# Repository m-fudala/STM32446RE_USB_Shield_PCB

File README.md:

# USB shield for Nucleo STM32F446RE
A simple shield which enables use of USB through type B receptacle. \
Includes also two places for THT resistors if external USB pull-ups are needed.

 \

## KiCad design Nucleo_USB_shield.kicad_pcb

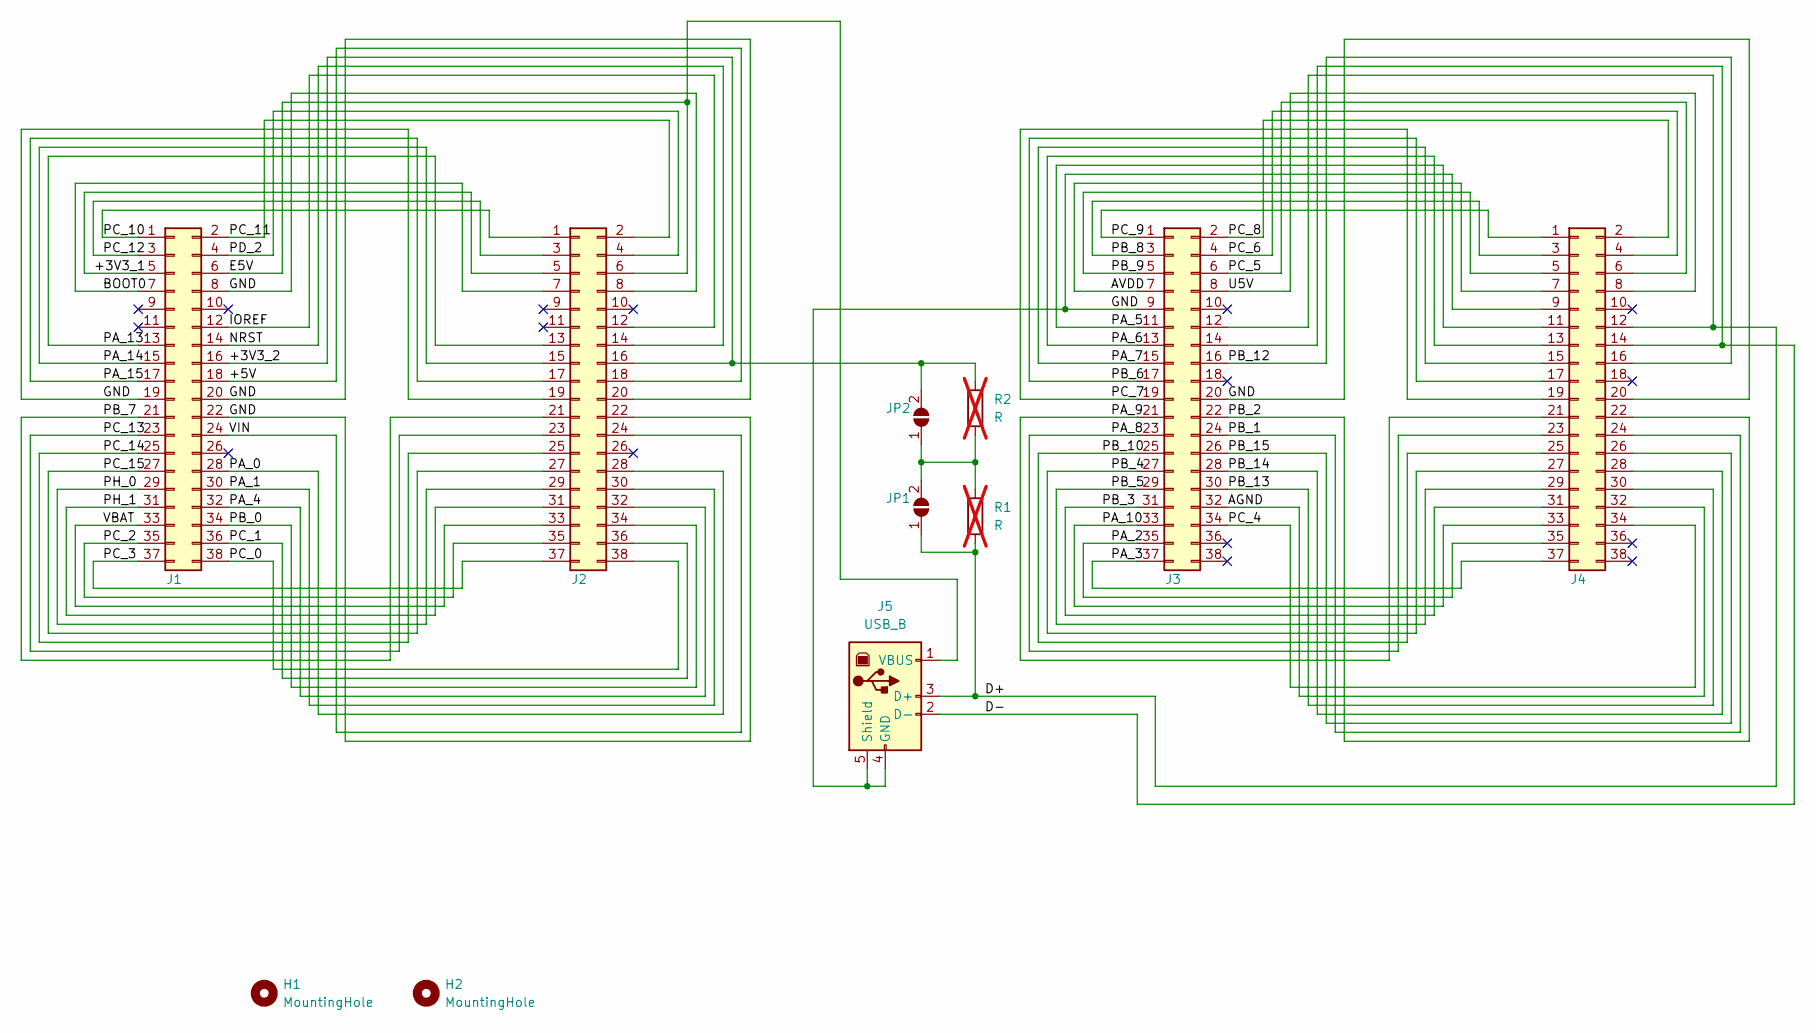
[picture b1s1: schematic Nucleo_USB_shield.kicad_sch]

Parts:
H1, H2: MountingHole; MountingHole_3.2mm_M3
J1, J3: Conn_02x19_Odd_Even; PinSocket_2x19_P2.54mm_Vertical
J2, J4: Conn_02x19_Odd_Even; PinHeader_2x19_P2.54mm_Vertical
J5: USB_B; USB_B_Lumberg_2411_02_Horizontal
JP1, JP2: SolderJumper_2_Open; SolderJumper-2_P1.3mm_Open_RoundedPad1.0x1.5mm
R1, R2: R; R_Axial_DIN0207_L6.3mm_D2.5mm_P7.62mm_Horizontal; not fitted

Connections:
/+3V3_1: J1.5, J2.5
/+3V3_2: J1.16, J2.16, JP2.2 (B), R2.1
/+5V: J1.18, J2.18
/AGND: J3.32, J4.32
/AVDD: J3.7, J4.7
/BOOT0: J1.7, J2.7
/D+: J3.12, J4.12, J5.3 (D+), JP1.1 (A), R1.2
/D-: J3.14, J4.14, J5.2 (D-)
/E5V: J1.6, J2.6, J5.1 (VBUS)
/GND: J1.8, J1.19, J1.20, J1.22, J2.8, J2.19, J2.20, J2.22, J3.9, J3.20, J4.9, J4.20, J5.4 (GND), J5.5 (Shield)
/IOREF: J1.12, J2.12
/NRST: J1.14, J2.14
/PA_0: J1.28, J2.28
/PA_1: J1.30, J2.30
/PA_2: J3.35, J4.35
/PA_3: J3.37, J4.37
/PA_4: J1.32, J2.32
/PA_5: J3.11, J4.11
/PA_6: J3.13, J4.13
/PA_7: J3.15, J4.15
/PA_8: J3.23, J4.23
/PA_9: J3.21, J4.21
/PA_10: J3.33, J4.33
/PA_13: J1.13, J2.13
/PA_14: J1.15, J2.15
/PA_15: J1.17, J2.17
/PB_0: J1.34, J2.34
/PB_1: J3.24, J4.24
/PB_2: J3.22, J4.22
/PB_3: J3.31, J4.31
/PB_4: J3.27, J4.27
/PB_5: J3.29, J4.29
/PB_6: J3.17, J4.17
/PB_7: J1.21, J2.21
/PB_8: J3.3, J4.3
/PB_9: J3.5, J4.5
/PB_10: J3.25, J4.25
/PB_12: J3.16, J4.16
/PB_13: J3.30, J4.30
/PB_14: J3.28, J4.28
/PB_15: J3.26, J4.26
/PC_0: J1.38, J2.38
/PC_1: J1.36, J2.36
/PC_2: J1.35, J2.35
/PC_3: J1.37, J2.37
/PC_4: J3.34, J4.34
/PC_5: J3.6, J4.6
/PC_6: J3.4, J4.4
/PC_7: J3.19, J4.19
/PC_8: J3.2, J4.2
/PC_9: J3.1, J4.1
/PC_10: J1.1, J2.1
/PC_11: J1.2, J2.2
/PC_12: J1.3, J2.3
/PC_13: J1.23, J2.23
/PC_14: J1.25, J2.25
/PC_15: J1.27, J2.27
/PD_2: J1.4, J2.4
/PH_0: J1.29, J2.29
/PH_1: J1.31, J2.31
/U5V: J3.8, J4.8
/VBAT: J1.33, J2.33
/VIN: J1.24, J2.24
unnamed: JP1.2 (B), JP2.1 (A), R1.1, R2.2

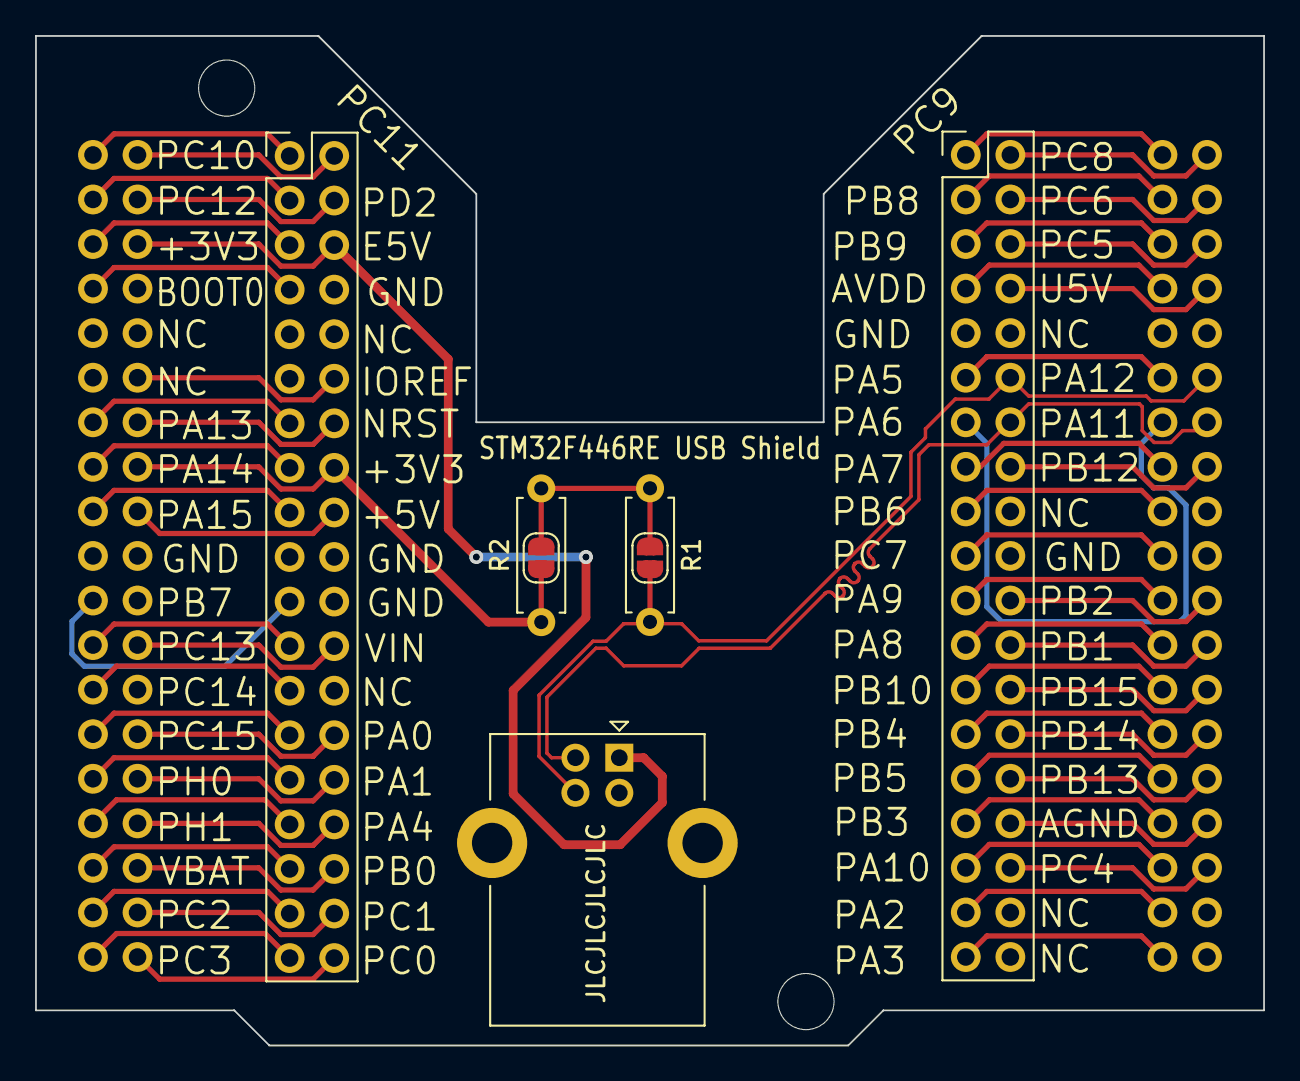
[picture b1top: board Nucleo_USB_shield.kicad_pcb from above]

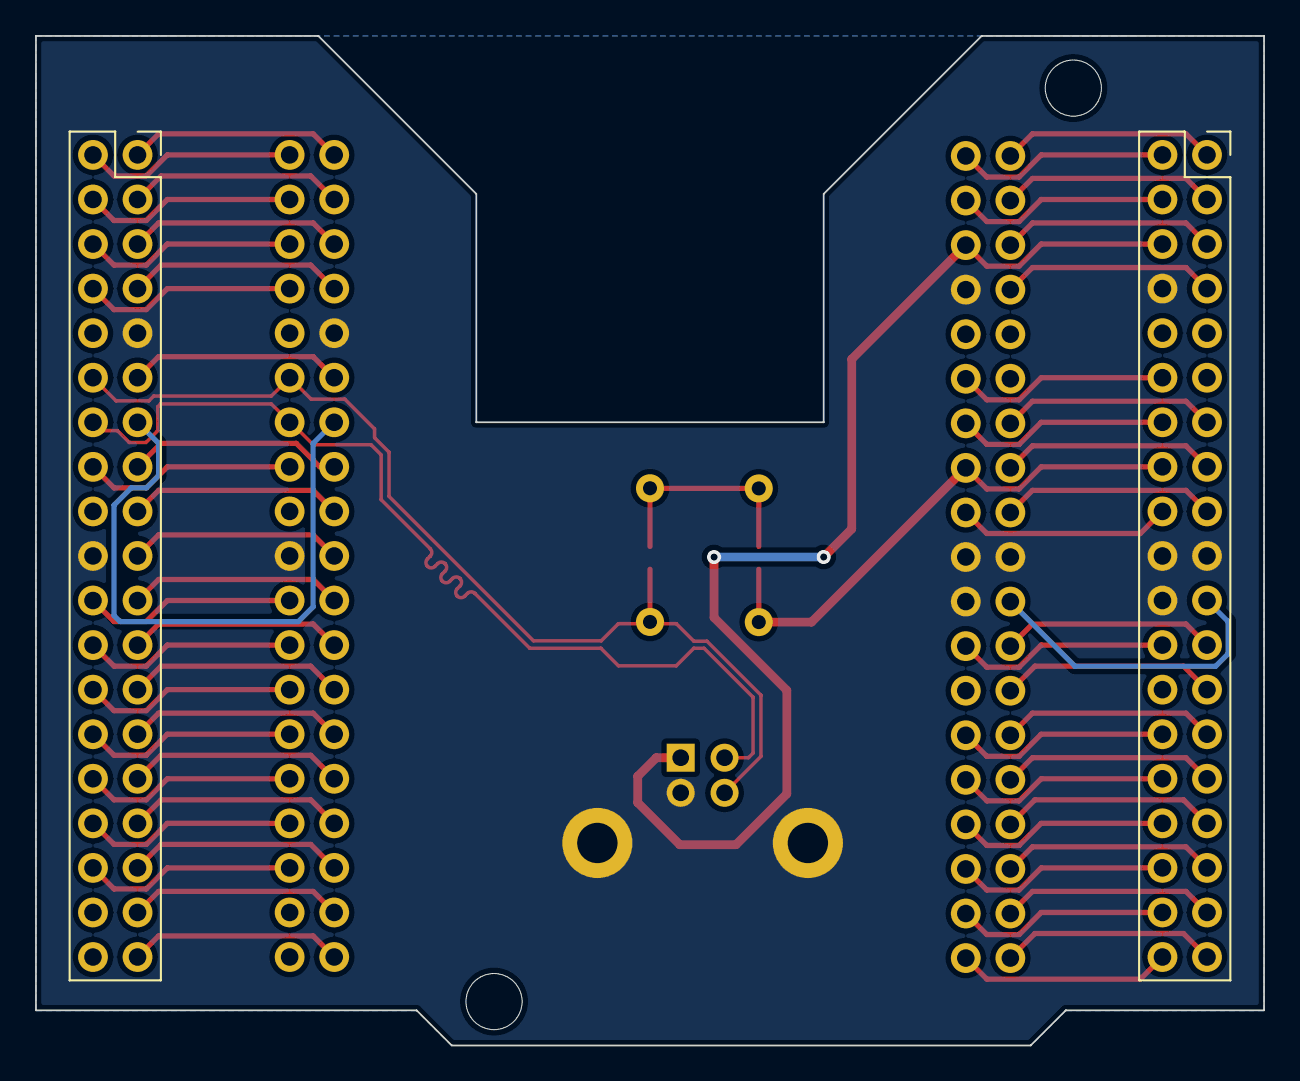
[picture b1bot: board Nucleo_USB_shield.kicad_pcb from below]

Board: 2 copper layers, 70.0 x 57.5 mm, 11 parts (2 on the bottom side), 64 nets.

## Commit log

2024-12-15 PCB ready
